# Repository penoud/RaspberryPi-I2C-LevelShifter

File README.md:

# RaspberryPi-I2C-LevelShifter
A i2c shifter based on TCA9517A IC

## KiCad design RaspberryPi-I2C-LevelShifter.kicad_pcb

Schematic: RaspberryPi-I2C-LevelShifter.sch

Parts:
C1, C3, C5, C6: 100nF
C2, C4: 1uF
P1: CONN_13X2
P2, P3: CONN_2
P4: CONN_4_GROVE
R1, R2: 4.7K
R3, R4: 10K
U1: TCA9517A

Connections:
+3V3: C3.1, C4.1, C5.1, P1.1, P1.17, R1.1, R2.1, U1.1 (VCC_A), U1.5 (EN)
+5V: C1.1, C2.1, C6.1, P1.2, P1.4, P4.3, R3.1, R4.1, U1.8 (VCC_B)
/SCL: P1.5, P2.2, U1.2 (SCLA)
/SCL_GROVE: P4.1, R4.2, U1.7 (SCLB)
/SDA: P1.3, P3.2, U1.3 (SDAA)
/SDA_GROVE: P4.2, R3.2, U1.6 (SDAB)
GND: C1.2, C2.2, C3.2, C4.2, C5.2, C6.2, P1.6, P1.9, P1.14, P1.20, P1.25, P4.4, U1.4 (GND)
unnamed: P2.1, R1.2
unnamed: P3.1, R2.2

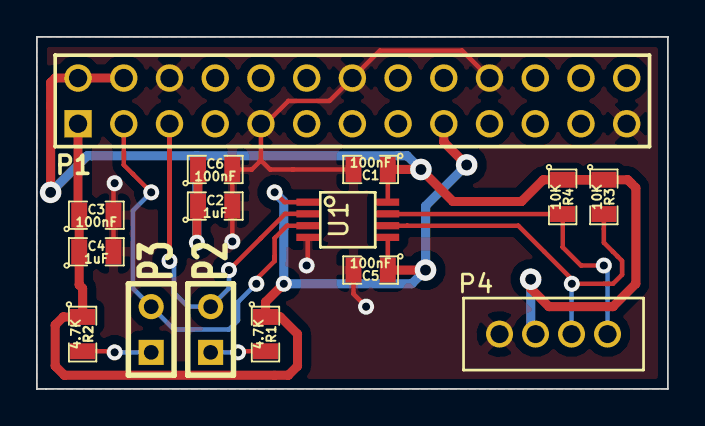
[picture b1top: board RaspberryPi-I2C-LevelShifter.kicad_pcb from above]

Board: 2 copper layers, 35.1 x 19.6 mm, 15 parts (0 on the bottom side), 9 nets.

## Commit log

2015-07-17 first revision
2015-07-28 correct according last library changes
